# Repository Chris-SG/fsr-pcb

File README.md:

## fsr-pcb

Collection of PCBs used in the fsr project

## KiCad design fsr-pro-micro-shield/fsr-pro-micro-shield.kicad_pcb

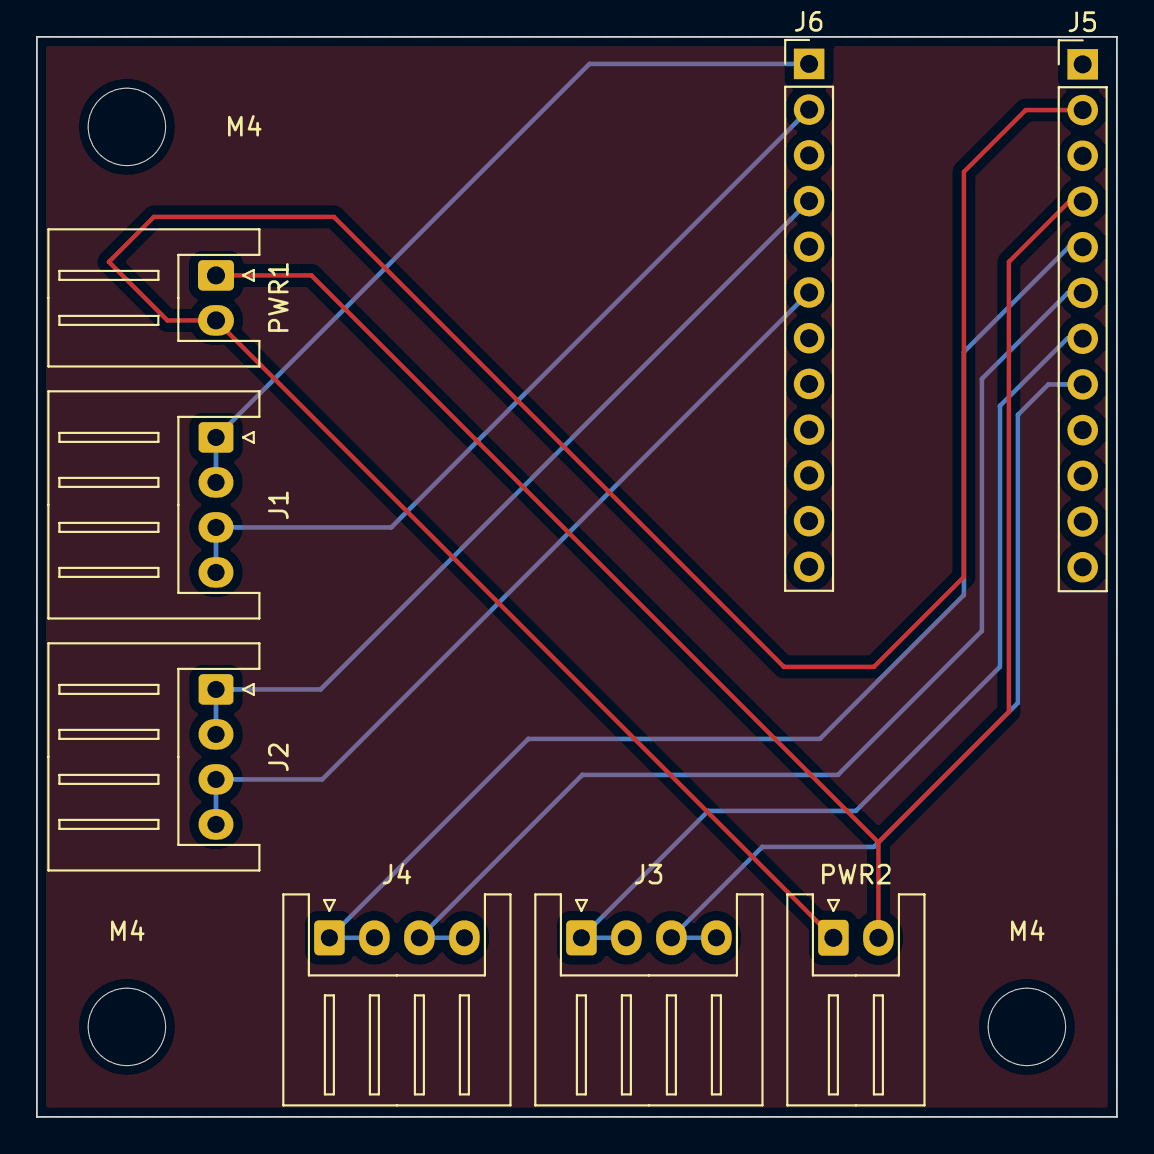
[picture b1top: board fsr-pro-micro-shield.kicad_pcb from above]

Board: 2 copper layers, 60.0 x 60.0 mm, 11 parts (0 on the bottom side), 10 nets.

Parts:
J1, J2, J3, J4: Conn_01x04_Male; JST_XH_S4B-XH-A_1x04_P2.50mm_Horizontal
J5, J6: Conn_01x12_Male; PinHeader_1x12_P2.54mm_Vertical
M4, M4#2, M4#3: MountingHole_4.3mm_M4
PWR1, PWR2: Conn_01x02_Male; JST_XH_S2B-XH-A_1x02_P2.50mm_Horizontal

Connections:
unnamed: J1.1, J1.2, J6.1
unnamed: J1.3, J1.4, J6.2
unnamed: J2.1, J2.2, J6.4
unnamed: J2.3, J2.4, J6.6
unnamed: J5.2, PWR1.2, PWR2.1
unnamed: J5.4, PWR1.1, PWR2.2
unnamed: J4.1, J4.2, J5.5
unnamed: J4.3, J4.4, J5.6
unnamed: J3.1, J3.2, J5.7
unnamed: J3.3, J3.4, J5.8

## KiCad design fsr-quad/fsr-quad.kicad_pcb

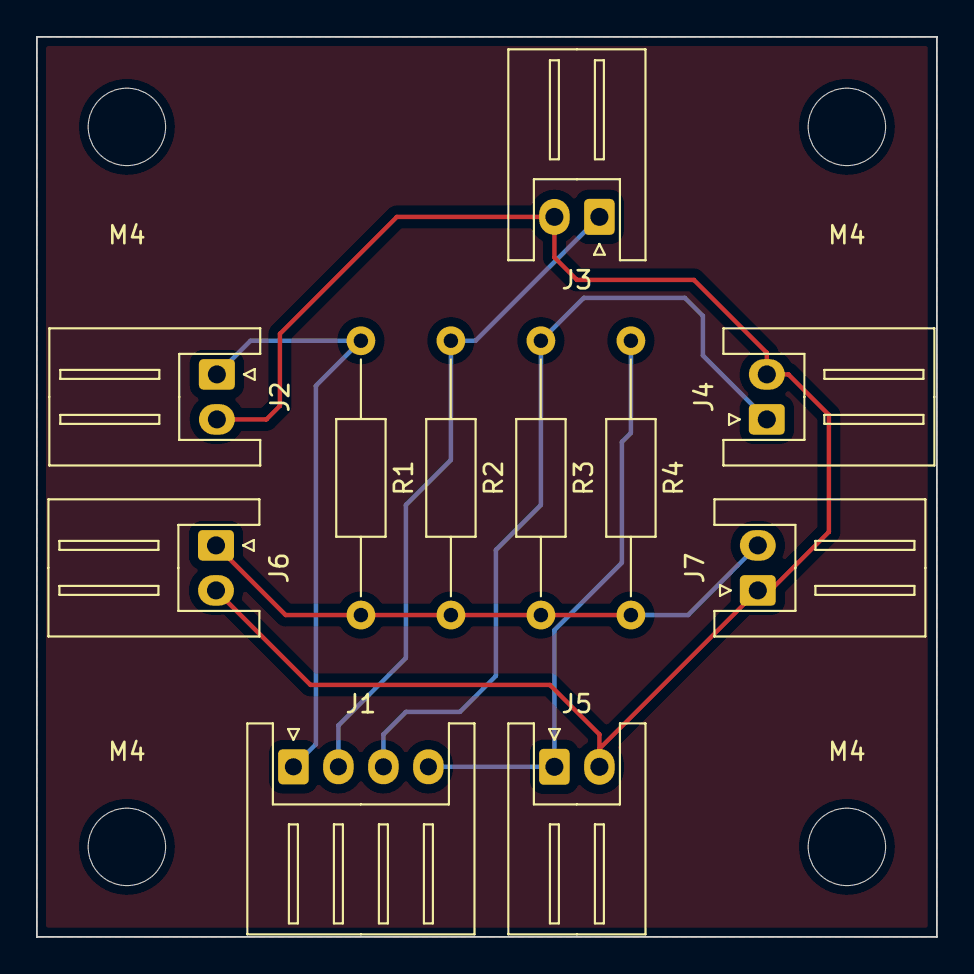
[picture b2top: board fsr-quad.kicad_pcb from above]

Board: 2 copper layers, 50.0 x 50.0 mm, 15 parts (0 on the bottom side), 6 nets.

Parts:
J1: Conn_01x04_Male; JST_XH_S4B-XH-A_1x04_P2.50mm_Horizontal
J2, J3, J4, J5, J6, J7: Conn_01x02_Male; JST_XH_S2B-XH-A_1x02_P2.50mm_Horizontal
M4, M4#2, M4#3, M4#4: MountingHole_4.3mm_M4
R1, R2, R3, R4: R; R_Axial_DIN0207_L6.3mm_D2.5mm_P15.24mm_Horizontal

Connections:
unnamed: J1.3, J4.1, R3.1
unnamed: J1.4, J5.1, R4.1
unnamed: J2.2, J3.2, J4.2, J5.2, J6.2, J7.1
unnamed: J6.1, J7.2, R1.2, R2.2, R3.2, R4.2
unnamed: J1.1, J2.1, R1.1
unnamed: J1.2, J3.1, R2.1

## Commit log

2022-06-19 Add pro micro shield
